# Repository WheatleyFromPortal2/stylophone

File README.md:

# stylophone

custom stylophone PCB

using [this guide](https://www.allaboutcircuits.com/projects/create-your-own-stylus-controlled-synthesizer/)

# PCB

PCB used will be 200mm by 150mm

## key footprints

each key has its own footprint (named P1-P7)

- 7mm border on the outside of the keys
- 1.5mm border between keys (there are 14 borders)
- every key is 11mm wide (there are 15 full keys across)
- each chamfer is 2mm x/y
- full-height keys are 35mm tall
- half-height keys (black keys) are 13mm tall
- footprint editor origin is at top left of key
- no rounding corners

**NOTE**: press E on a pad to edit it
- use [this link](https://forum.kicad.info/t/create-pad-from-selected-shapes-solved/32770) to figure out the pad footprint
- [also useful](https://learn.pcbcupid.com/pcb-design/design/kicad/custom-footprints-in-kicad)

# TODO

1. [x] add custom footprints for `TP4`-`TP28` so that they look like a keyboard in the PCB
	- plan pad types for each key by annotating the example PCB
2. [x] layout PCB
3. [x] build BOM and order correct parts
4. [x] route PCB
5. [ ] assemble PCB
    - need to make a stylus with a solder ball at the end
    - an alligator clip is way to abrasive and wears through the copper layer quickly
6. [ ] test PCB

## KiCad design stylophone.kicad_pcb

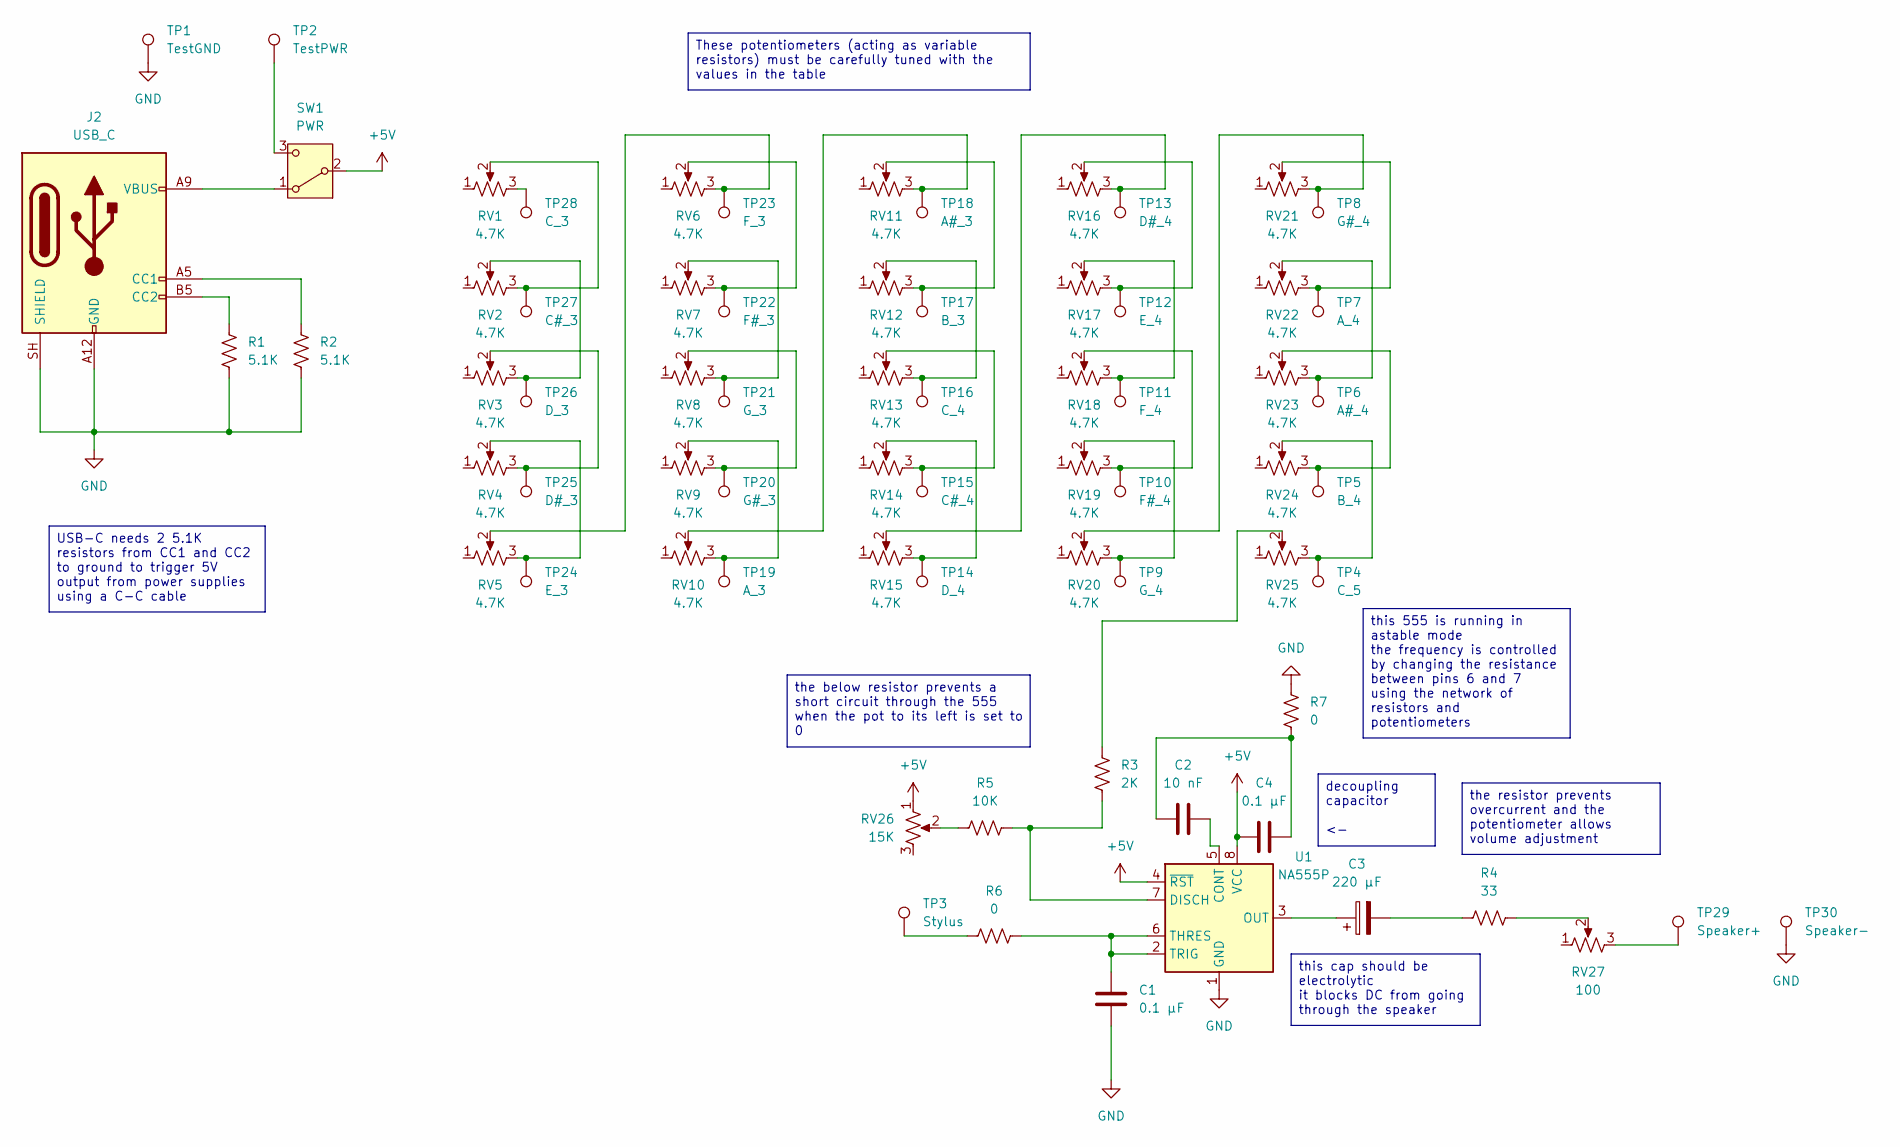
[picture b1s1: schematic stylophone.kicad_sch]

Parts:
C1, C4: 0.1 μF; C_Rect_L10.0mm_W3.0mm_P7.50mm_FKS3_FKP3
C2: 10 nF; C_Rect_L10.0mm_W3.0mm_P7.50mm_FKS3_FKP3
C3: 220 μF; CP_Radial_D6.3mm_P2.50mm
J2: USB_C; USB_C_Receptacle_GCT_USB4125-xx-x-0190_6P_TopMnt_Horizontal
R1, R2: 5.1K; R_Axial_DIN0204_L3.6mm_D1.6mm_P7.62mm_Horizontal
R3: 2K; R_Axial_DIN0204_L3.6mm_D1.6mm_P7.62mm_Horizontal
R4: 33; R_Axial_DIN0204_L3.6mm_D1.6mm_P7.62mm_Horizontal
R5: 10K; R_Axial_DIN0204_L3.6mm_D1.6mm_P7.62mm_Horizontal
R6, R7: 0; R_Axial_DIN0204_L3.6mm_D1.6mm_P7.62mm_Horizontal
RV1, RV2, RV3, RV4, RV5, RV6, RV7, RV8, RV9, RV10, RV11, RV12, RV13, RV14, RV15, RV16, RV17, RV18, RV19, RV20, RV21, RV22, RV23, RV24, RV25: 4.7K; Potentiometer_Bourns_3296W_Vertical
RV26: 15K; Potentiometer_Bourns_3296W_Vertical
RV27: 100; Potentiometer_Bourns_3296W_Vertical
SW1: PWR; SW_Slide_SPDT_Straight_CK_OS102011MS2Q
TP1: TestGND; TestPoint_THTPad_D2.0mm_Drill1.0mm
TP2: TestPWR; TestPoint_THTPad_D2.0mm_Drill1.0mm
TP3: Stylus; TestPoint_THTPad_D2.0mm_Drill1.0mm
TP4: C_5; P1
TP5: B_4; P2
TP6: A#_4; P3
TP7: A_4; P4
TP8: G#_4; P5
TP9: G_4; P4
TP10: F#_4; P6
TP11: F_4; P7
TP12: E_4; P2
TP13: D#_4; P3
TP14: D_4; P4
TP15: C#_4; P6
TP16: C_4; P7
TP17: B_3; P2
TP18: A#_3; P3
TP19: A_3; P4
TP20: G#_3; P5
TP21: G_3; P4
TP22: F#_3; P6
TP23: F_3; P7
TP24: E_3; P2
TP25: D#_3; P3
TP26: D_3; P4
TP27: C#_3; P6
TP28: C_3; P7
TP29: Speaker+; TestPoint_THTPad_D2.0mm_Drill1.0mm
TP30: Speaker-; TestPoint_THTPad_D2.0mm_Drill1.0mm
U1: NA555P; DIP-8_W7.62mm

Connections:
+5V: C4.2, RV26.1, SW1.2 (B), U1.4 (~RST), U1.8 (VCC)
GND: C1.1, J2.A12 (GND), J2.B12 (GND), J2.SH (SHIELD), R1.2, R2.2, R7.1, TP1.1 (1_1), TP30.1 (1_1), U1.1 (GND)
unnamed: C2.1, C4.1, R7.2
unnamed: C3.2, R4.1
unnamed: J2.A5 (CC1), R2.1
unnamed: J2.B5 (CC2), R1.1
unnamed: R3.1, RV25.2
unnamed: R4.2, RV27.2
unnamed: R5.1, RV26.2
unnamed: R6.1, TP3.1 (1_1)
unnamed: RV1.2, RV2.3, TP27.1 (1_1)
unnamed: RV1.3, TP28.1 (1_1)
unnamed: RV2.2, RV3.3, TP26.1 (1_1)
unnamed: RV3.2, RV4.3, TP25.1 (1_1)
unnamed: RV4.2, RV5.3, TP24.1 (1_1)
unnamed: RV5.2, RV6.3, TP23.1 (1_1)
unnamed: RV6.2, RV7.3, TP22.1 (1_1)
unnamed: RV7.2, RV8.3, TP21.1 (1_1)
unnamed: RV8.2, RV9.3, TP20.1 (1_1)
unnamed: RV10.2, RV11.3, TP18.1 (1_1)
unnamed: RV9.2, RV10.3, TP19.1 (1_1)
unnamed: RV11.2, RV12.3, TP17.1 (1_1)
unnamed: RV12.2, RV13.3, TP16.1 (1_1)
unnamed: RV13.2, RV14.3, TP15.1 (1_1)
unnamed: RV14.2, RV15.3, TP14.1 (1_1)
unnamed: RV15.2, RV16.3, TP13.1 (1_1)
unnamed: RV16.2, RV17.3, TP12.1 (1_1)
unnamed: RV17.2, RV18.3, TP11.1 (1_1)
unnamed: RV18.2, RV19.3, TP10.1 (1_1)
unnamed: RV19.2, RV20.3, TP9.1 (1_1)
unnamed: RV20.2, RV21.3, TP8.1 (1_1)
unnamed: RV21.2, RV22.3, TP7.1 (1_1)
unnamed: RV22.2, RV23.3, TP6.1 (1_1)
unnamed: RV23.2, RV24.3, TP5.1 (1_1)
unnamed: RV24.2, RV25.3, TP4.1 (1_1)
unnamed: RV27.3, TP29.1 (1_1)
unnamed: J2.A9 (VBUS), J2.B9 (VBUS), SW1.1 (A)
unnamed: SW1.3 (C), TP2.1 (1_1)
unnamed: C2.2, U1.5 (CONT)
unnamed: R3.2, R5.2, U1.7 (DISCH)
unnamed: C3.1, U1.3 (OUT)
unnamed: C1.2, R6.2, U1.2 (TRIG), U1.6 (THRES)

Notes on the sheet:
this 555 is running in astable mode the frequency is controlled by changing the resistance between pins 6 and 7 using the network of resistors and potentiometers
the below resistor prevents a short circuit through the 555 when the pot to its left is set to 0
These potentiometers (acting as variable resistors) must be carefully tuned with the values in the table
this cap should be electrolytic it blocks DC from going through the speaker
the resistor prevents overcurrent and the potentiometer allows volume adjustment
USB-C needs 2 5.1K resistors from CC1 and CC2 to ground to trigger 5V output from power supplies using a C-C cable
decoupling capacitor <-

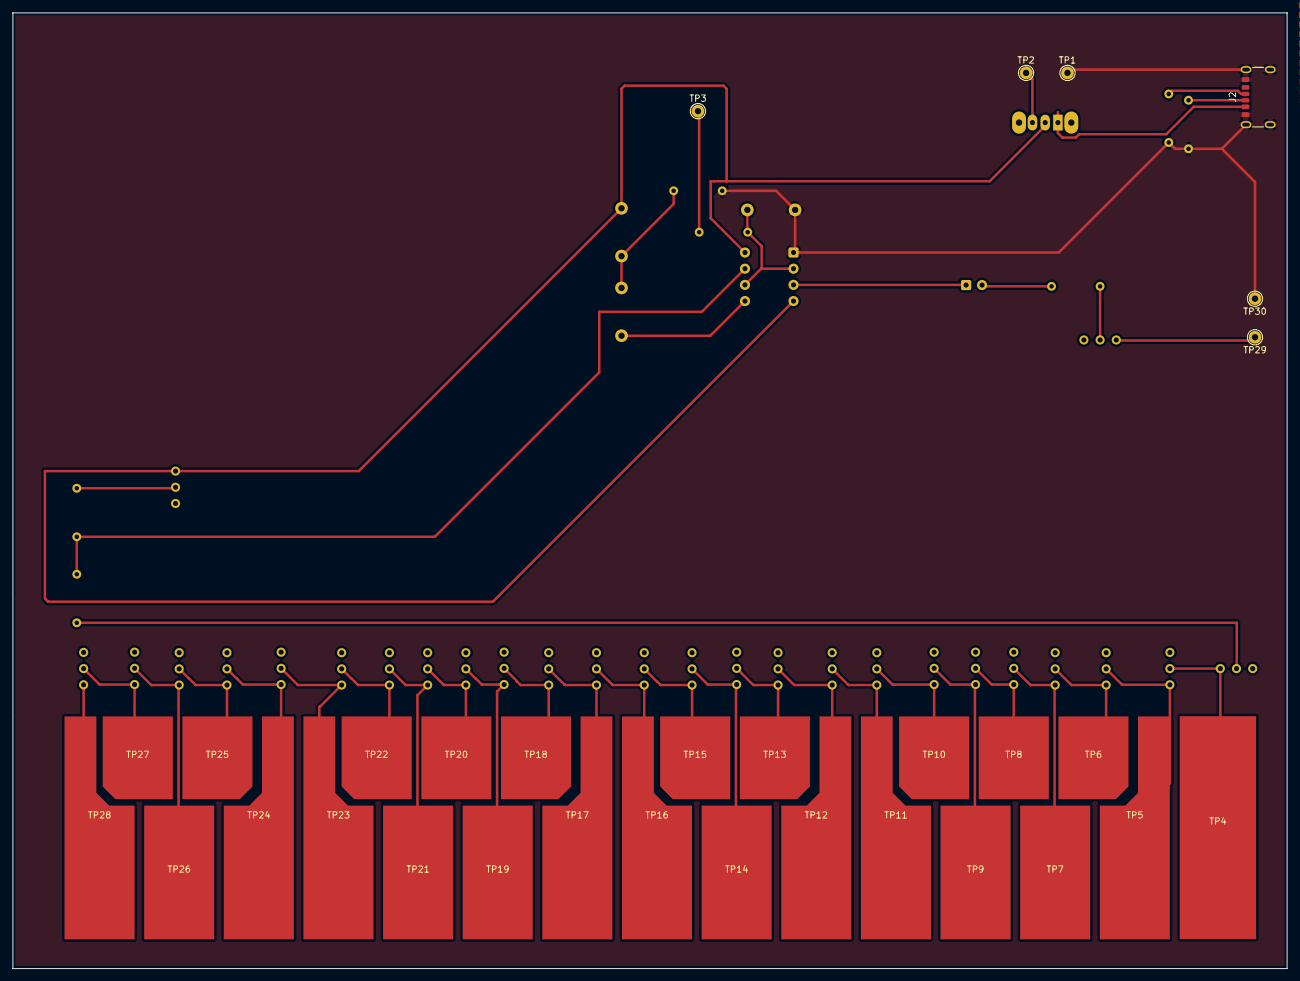
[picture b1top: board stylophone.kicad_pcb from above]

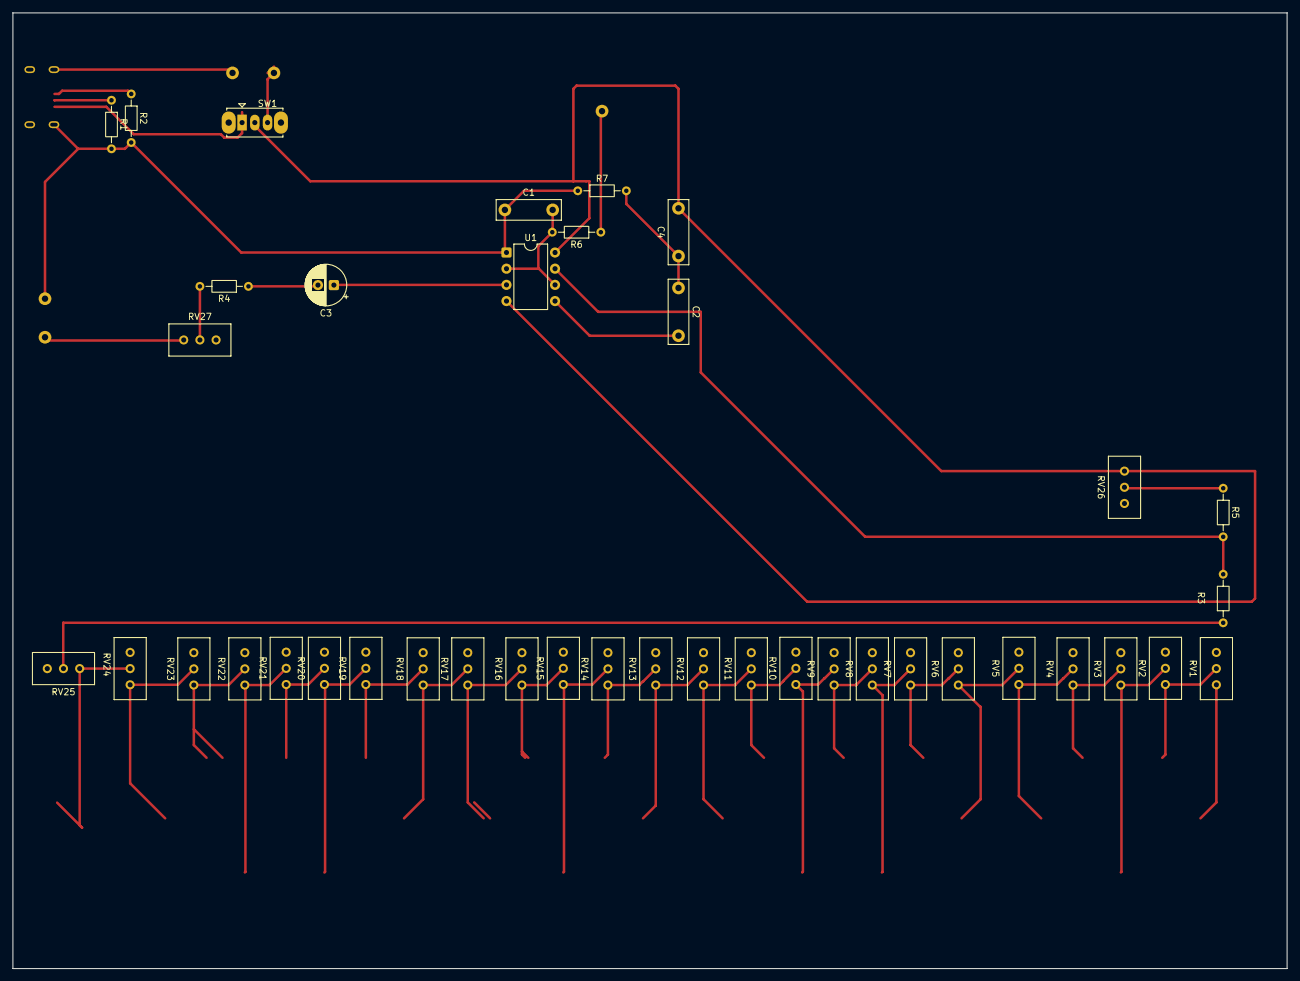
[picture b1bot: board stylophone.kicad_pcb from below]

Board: 2 copper layers, 200.0 x 150.0 mm, 71 parts (40 on the bottom side), 42 nets.
